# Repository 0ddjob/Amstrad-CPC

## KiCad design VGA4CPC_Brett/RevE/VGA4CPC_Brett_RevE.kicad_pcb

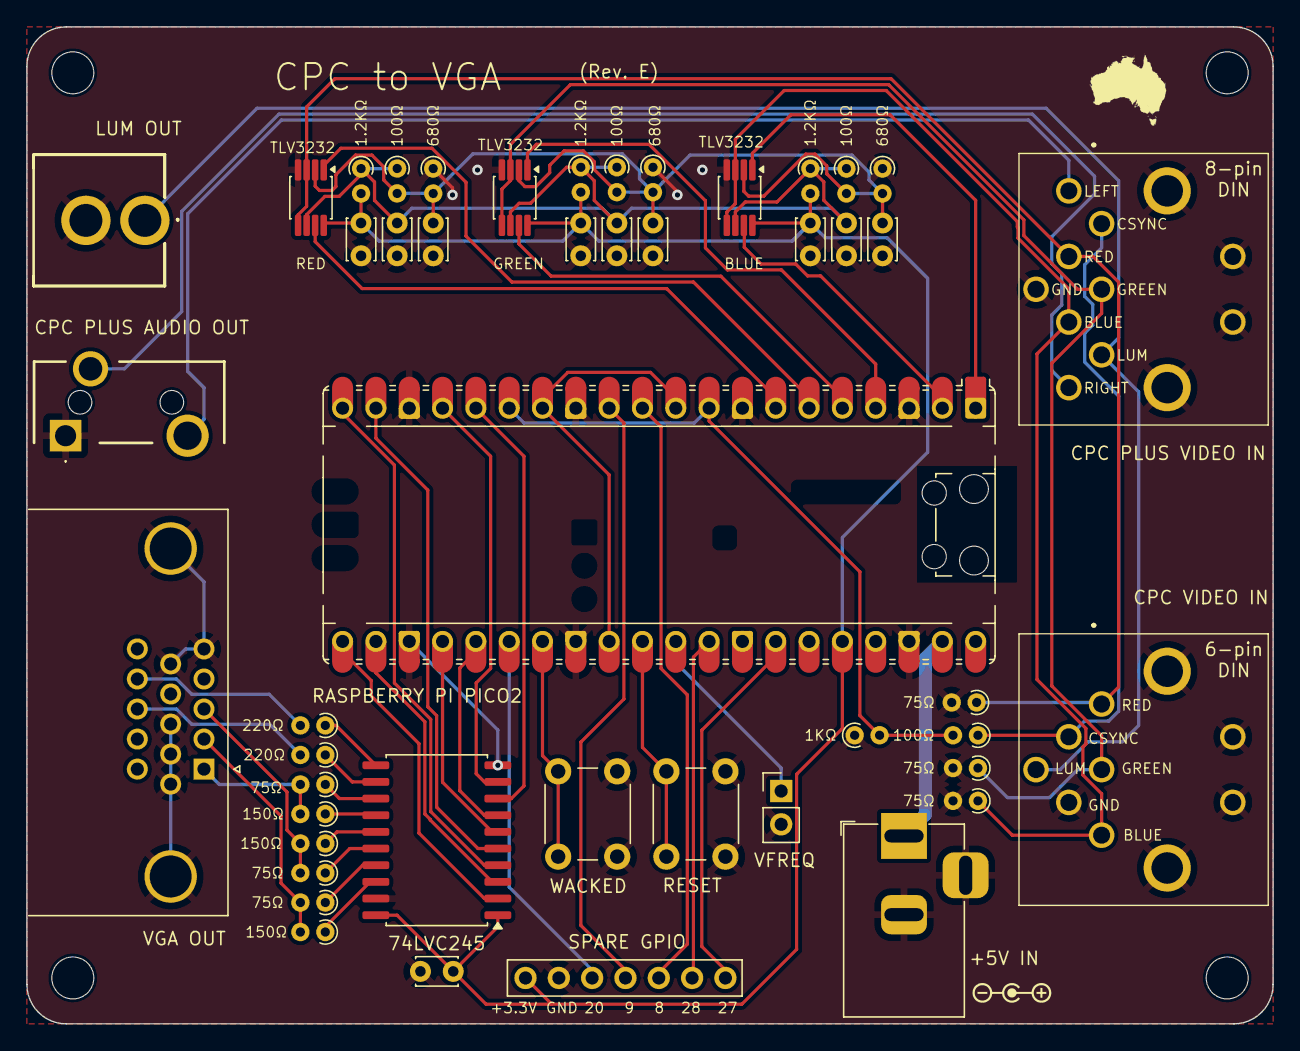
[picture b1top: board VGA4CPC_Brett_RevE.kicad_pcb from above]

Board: 2 copper layers, 95.0 x 76.0 mm, 51 parts (0 on the bottom side), 49 nets.

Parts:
C1, C2, C3, C4, C5, C6, C7, C8, C9, C10: 100nF; C_Disc_D3.0mm_W2.0mm_P2.50mm
H1, H2, H3, H4: MountingHole; MountingHole_3.2mm_M3
J1: CPC VIDEO IN; SDF80J
J2: LUM OUT; 1560099E
J3: +5V IN; BarrelJack_Horizontal
J4: VFREQ; PinHeader_1x02_P2.54mm_Vertical
J5: SPARE GPIO; PinHeader_1x07_P2.54mm_Vertical
J6: VGA OUT; DSUB-15-HD_Socket_Horizontal_P2.29x2.54mm_EdgePinOffset8.35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
J7: CPC PLUS VIDEO IN; SDF80J
J8: CPC PLUS AUDIO OUT; SJ335083ATR
R1, R2, R3, R7, R8, R11: 75Ω; R_Axial_DIN0204_L3.6mm_D1.6mm_P1.90mm_Vertical
R4, R16, R18, R21: 100Ω; R_Axial_DIN0204_L3.6mm_D1.6mm_P1.90mm_Vertical
R5: 1KΩ; R_Axial_DIN0204_L3.6mm_D1.6mm_P1.90mm_Vertical
R6, R9, R10: 150Ω; R_Axial_DIN0204_L3.6mm_D1.6mm_P1.90mm_Vertical
R12, R13: 220Ω; R_Axial_DIN0204_L3.6mm_D1.6mm_P1.90mm_Vertical
R14, R15, R20: 1.2KΩ; R_Axial_DIN0204_L3.6mm_D1.6mm_P1.90mm_Vertical
R17, R19, R22: 680Ω; R_Axial_DIN0204_L3.6mm_D1.6mm_P1.90mm_Vertical
SW1: RESET; SW_PUSH_6mm
SW2: WACKED; SW_PUSH_6mm
U1: RASPBERRY PI PICO2; RaspberryPi_Pico_Common_Unspecified
U2: 74LVC245; SOIC-20W_7.5x12.8mm_P1.27mm
U3, U4, U5: TLV3232; VSSOP-8_3x3mm_P0.65mm

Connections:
+3.3V: C1.2, C7.1, C9.1, C10.1, J5.7, R14.2, R15.2, R20.2, U1.36 (3V3), U2.1 (A->B), U2.20 (VCC), U3.8 (VCC), U4.8 (VCC), U5.8 (VCC)
+5V: J3.1, U1.39 (VSYS)
/B_{0}: U1.1 (GPIO0), U3.1 (1OUT)
/B_{1}: U1.2 (GPIO1), U3.7 (2OUT)
/CPC_AUDIO_L: J7.6, J8.T
/CPC_AUDIO_R: J7.7, J8.R
/CPC_B: J1.3, J7.5, R1.1, U3.3 (1IN+), U3.5 (2IN+)
/CPC_CSYNC: J1.4, J7.1, R4.1
/CPC_G: J1.2, J7.2, R2.1, U5.3 (1IN+), U5.5 (2IN+)
/CPC_LUM: J1.6, J2.1 (In), J7.3
/CPC_R: J1.1, J7.4, R3.1, U4.3 (1IN+), U4.5 (2IN+)
/CSYNC: R4.2, R5.2, U1.9 (GPIO6), U1.15 (GPIO11)
/GPIO8: J5.3, U1.11 (GPIO8)
/GPIO9: J5.4, U1.12 (GPIO9)
/GPIO20: J5.5, U1.26 (GPIO20)
/GPIO27: J5.2, U1.32 (GPIO27_ADC1)
/GPIO28: J5.1, U1.34 (GPIO28_ADC2)
/G_{0}: U1.4 (GPIO2), U5.1 (1OUT)
/G_{1}: U1.5 (GPIO3), U5.7 (2OUT)
/INT_VSYNC: U1.10 (GPIO7), U1.14 (GPIO10), U1.29 (GPIO22)
/LOWER: C2.1, C3.1, C4.1, R16.2, R17.2, R18.2, R19.2, R21.2, R22.2, U3.2 (1IN-), U4.2 (1IN-), U5.2 (1IN-)
/R_{0}: U1.6 (GPIO4), U4.1 (1OUT)
/R_{1}: U1.7 (GPIO5), U4.7 (2OUT)
/UPPER: C5.1, C6.1, C8.1, R14.1, R15.1, R16.1, R18.1, R20.1, R21.1, U3.6 (2IN-), U4.6 (2IN-), U5.6 (2IN-)
/VGA_B: J6.3, R8.2, R9.2
/VGA_B_{0}: U1.19 (GPIO14), U2.5 (A3)
/VGA_B_{1}: U1.20 (GPIO15), U2.4 (A2)
/VGA_G: J6.2, R6.2, R7.2
/VGA_G_{0}: U1.21 (GPIO16), U2.2 (A0)
/VGA_G_{1}: U1.22 (GPIO17), U2.3 (A1)
/VGA_HSYNC: U1.16 (GPIO12), U2.8 (A6)
/VGA_HSYNC_{B}: J6.13, R12.2
/VGA_R: J6.1, R10.2, R11.2
/VGA_R_{0}: U1.24 (GPIO18), U2.6 (A4)
/VGA_R_{1}: U1.25 (GPIO19), U2.7 (A5)
/VGA_VSYNC: U1.17 (GPIO13), U2.9 (A7)
/VGA_VSYNC_{B}: J6.14, R13.2
GND: C1.1, C2.2, C3.2, C4.2, C5.2, C6.2, C7.2, C8.2, C9.2, C10.2, J1.5, J2.2 (Ext), J3.2, J4.2, J5.6, J6.0, J6.5, J6.6, J6.7, J6.8, J6.10, J7.8, J8.S, R1.2, R2.2, R3.2, R5.1, R17.1, R19.1, R22.1, SW1.1, SW2.2, U1.3 (GND), U1.8 (GND), U1.13 (GND), U1.18 (GND), U1.23 (GND), U1.28 (GND), U1.38 (GND), U2.10 (GND), U2.19 (CE), U3.4 (GND), U4.4 (GND), U5.4 (GND)
unnamed: J4.1, U1.31 (GPIO26_ADC0)
unnamed: SW2.1, U1.27 (GPIO21)
unnamed: SW1.2, U1.30 (RUN)
unnamed: R6.1, U2.18 (B0)
unnamed: R7.1, U2.17 (B1)
unnamed: R8.1, U2.16 (B2)
unnamed: R9.1, U2.15 (B3)
unnamed: R10.1, U2.14 (B4)
unnamed: R11.1, U2.13 (B5)
unnamed: R12.1, U2.12 (B6)
unnamed: R13.1, U2.11 (B7)

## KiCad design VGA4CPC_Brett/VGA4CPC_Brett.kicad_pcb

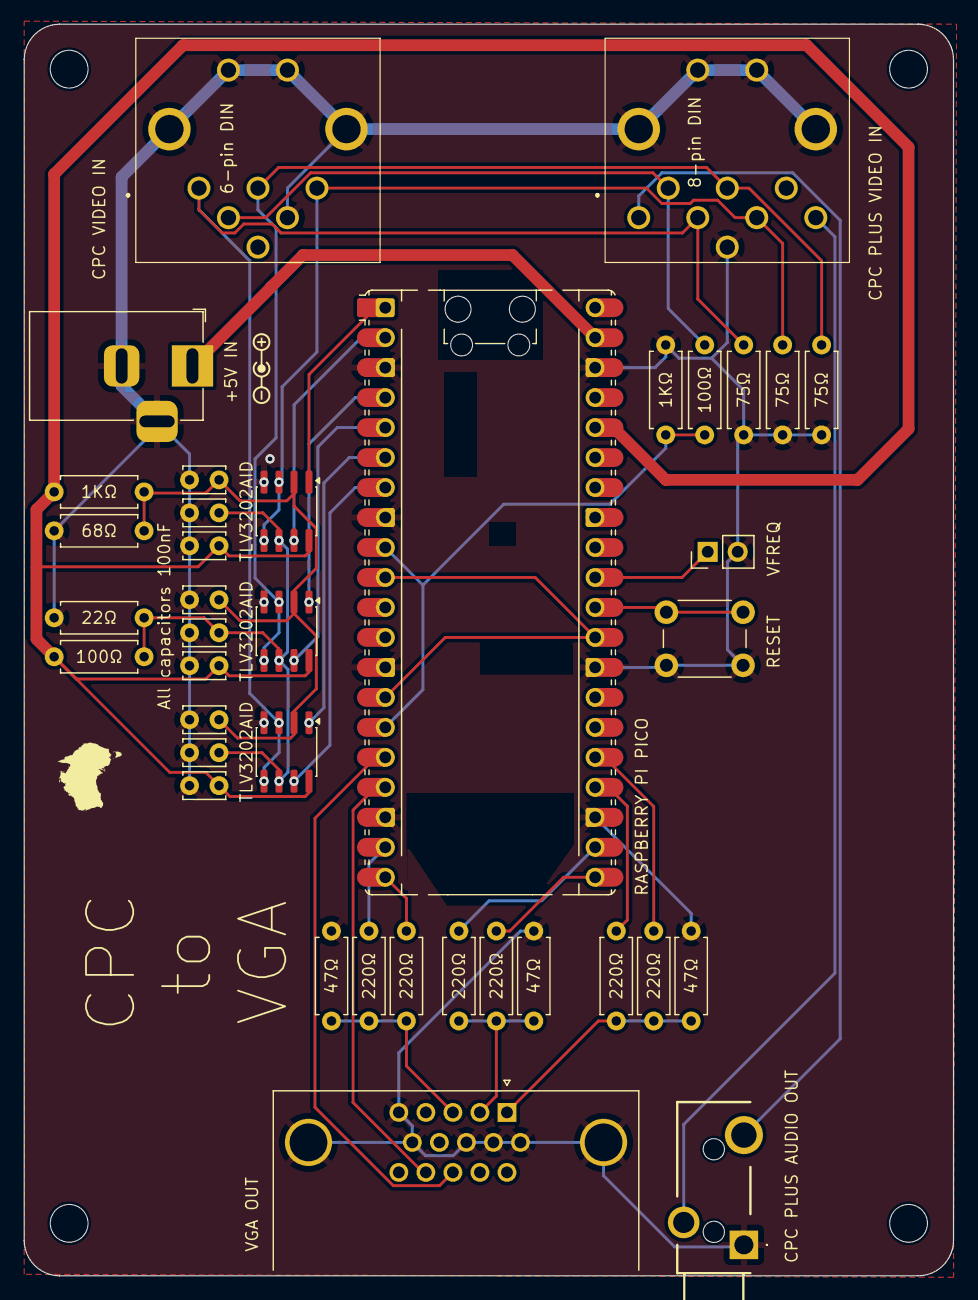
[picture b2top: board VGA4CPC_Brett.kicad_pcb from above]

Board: 2 copper layers, 78.7 x 106.0 mm, 42 parts (0 on the bottom side), 32 nets.

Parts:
C1, C2, C3, C4, C5, C6, C7, C8, C9: 100nF; C_Disc_D3.4mm_W2.1mm_P2.50mm
H1, H2, H3, H4: MountingHole; MountingHole_3.2mm_M3
J1: +5V IN; BarrelJack_Horizontal
J2: CPC PLUS AUDIO OUT; SJ335083ATR
J3: CPC PLUS VIDEO IN; SDF80J
J4: CPC VIDEO IN; SDF80J
J5: VFREQ; PinHeader_1x02_P2.54mm_Vertical
J6: VGA OUT; DSUB-15-HD_Socket_Horizontal_P2.29x2.54mm_EdgePinOffset8.35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
R1, R13: 1KΩ; R_Axial_DIN0207_L6.3mm_D2.5mm_P7.62mm_Horizontal
R2, R12: 100Ω; R_Axial_DIN0207_L6.3mm_D2.5mm_P7.62mm_Horizontal
R3: 68Ω; R_Axial_DIN0207_L6.3mm_D2.5mm_P7.62mm_Horizontal
R4: 22Ω; R_Axial_DIN0207_L6.3mm_D2.5mm_P7.62mm_Horizontal
R5, R14, R18: 75Ω; R_Axial_DIN0207_L6.3mm_D2.5mm_P7.62mm_Horizontal
R6, R8, R9, R11, R15, R17: 220Ω; R_Axial_DIN0207_L6.3mm_D2.5mm_P7.62mm_Horizontal
R7, R10, R16: 47Ω; R_Axial_DIN0207_L6.3mm_D2.5mm_P7.62mm_Horizontal
SW1: RESET; SW_PUSH_6mm
U1, U2, U4: TLV3202AID; SOIC-8_3.9x4.9mm_P1.27mm
U3: RASPBERRY PI PICO; RaspberryPi_Pico_Common_Unspecified

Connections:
+3.3V: C1.1, C4.1, C7.1, R1.1, R2.1, U1.8 (VCC), U2.8 (VCC), U3.36 (3V3), U4.8 (VCC)
+5V: J1.1, U3.39 (VSYS)
/200mV: C2.1, C5.1, C8.1, R1.2, R3.1, U1.2 (1IN-), U2.2 (1IN-), U4.2 (1IN-)
/600mV: C3.1, C6.1, C9.1, R2.2, R4.1, U1.6 (2IN-), U2.6 (2IN-), U4.6 (2IN-)
/B_{0}: U1.1 (1OUT), U3.1 (GPIO0)
/B_{1}: U1.7 (2OUT), U3.2 (GPIO1)
/CPC_AUDIO_L: J2.T, J3.6
/CPC_AUDIO_R: J2.R, J3.7
/CPC_B: J3.5, J4.3, R5.1, U1.3 (1IN+), U1.5 (2IN+)
/CPC_CSYNC: J3.1, J4.4, R12.1
/CPC_G: J3.2, J4.2, R14.1, U2.3 (1IN+), U2.5 (2IN+)
/CPC_R: J3.4, J4.1, R18.1, U4.3 (1IN+), U4.5 (2IN+)
/CSYNC: R12.2, R13.1, U3.9 (GPIO6), U3.15 (GPIO11)
/G_{0}: U2.1 (1OUT), U3.4 (GPIO2)
/G_{1}: U2.7 (2OUT), U3.5 (GPIO3)
/INT_VSYNC: U3.10 (GPIO7), U3.14 (GPIO10), U3.29 (GPIO22)
/R_{0}: U3.6 (GPIO4), U4.1 (1OUT)
/R_{1}: U3.7 (GPIO5), U4.7 (2OUT)
/VGA_B: J6.3, R15.2, R16.2, R17.2
/VGA_G: J6.2, R6.2, R7.1, R8.2
/VGA_HSYNC: J6.13, U3.16 (GPIO12)
/VGA_R: J6.1, R9.2, R10.1, R11.2
/VGA_VSYNC: J6.14, U3.17 (GPIO13)
GND: C1.2, C2.2, C3.2, C4.2, C5.2, C6.2, C7.2, C8.2, C9.2, J1.2, J2.S, J3.8, J4.5, J5.2, J6.0, J6.5, J6.6, J6.7, J6.8, J6.10, R3.2, R4.2, R5.2, R7.2, R10.2, R13.2, R14.2, R16.1, R18.2, SW1.1, U1.4 (GND), U2.4 (GND), U3.3 (GND), U3.8 (GND), U3.13 (GND), U3.18 (GND), U3.23 (GND), U3.28 (GND), U3.38 (GND), U4.4 (GND)
unnamed: J5.1, U3.31 (GPIO26_ADC0)
unnamed: R15.1, U3.19 (GPIO14)
unnamed: R17.1, U3.20 (GPIO15)
unnamed: R6.1, U3.21 (GPIO16)
unnamed: R8.1, U3.22 (GPIO17)
unnamed: R9.1, U3.24 (GPIO18)
unnamed: R11.1, U3.25 (GPIO19)
unnamed: SW1.2, U3.30 (RUN)

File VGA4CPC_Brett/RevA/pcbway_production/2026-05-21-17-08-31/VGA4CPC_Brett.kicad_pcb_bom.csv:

Designator,Quantity,Value,Footprint,Package,MPN,DNP,Mount_Type,Description,Height,Mouser Part Number,Mouser Price/Stock,Manufacturer_Name
"C1, C2, C3, C4, C5, C6, C7, C8, C9",9,100nF,C_Disc_D3.4mm_W2.1mm_P2.50mm,,,,tht,,,,,
"H1, H2, H3, H4",4,MountingHole,MountingHole_3.2mm_M3,,,,tht,,,,,
J1,1,+5V IN,BarrelJack_Horizontal,,,,tht,DC Barrel Jack,,,,
J2,1,CPC PLUS AUDIO OUT,SJ335083ATR,,,,tht,"Audio Jack, 3 Poles (Stereo / TRS)",,,,
J3,1,CPC PLUS VIDEO IN,SDF80J,,,,tht,Same Sky SDF-80J 8-pin DIN socket,,,,
J4,1,CPC VIDEO IN,SDF80J,,,,tht,Same Sky SDF-60J 6-pin DIN Socket,,,,
J5,1,VFREQ,PinHeader_1x02_P2.54mm_Vertical,,,,tht,"Generic connector, single row, 01x02, script generated (kicad-library-utils/schlib/autogen/connector/)",,,,
J6,1,VGA OUT,DSUB-15-HD_Socket_Horizontal_P2.29x2.54mm_EdgePinOffset8.35mm_Housed_MountingHolesOffset10.89mm,,,,tht,"15-pin D-SUB connector, socket (female), High density (3 columns), Triple Row, Generic, VGA-connector, Mounting Hole",,,,
"R1, R13",2,1KΩ,R_Axial_DIN0207_L6.3mm_D2.5mm_P7.62mm_Horizontal,,,,tht,"Resistor, small symbol",,,,
"R10, R16, R7",3,47Ω,R_Axial_DIN0207_L6.3mm_D2.5mm_P7.62mm_Horizontal,,,,tht,"Resistor, small symbol",,,,
"R11, R15, R17, R6, R8, R9",6,220Ω,R_Axial_DIN0207_L6.3mm_D2.5mm_P7.62mm_Horizontal,,,,tht,"Resistor, small symbol",,,,
"R12, R2",2,100Ω,R_Axial_DIN0207_L6.3mm_D2.5mm_P7.62mm_Horizontal,,,,tht,"Resistor, small symbol",,,,
"R14, R18, R5",3,75Ω,R_Axial_DIN0207_L6.3mm_D2.5mm_P7.62mm_Horizontal,,,,tht,"Resistor, small symbol",,,,
R3,1,68Ω,R_Axial_DIN0207_L6.3mm_D2.5mm_P7.62mm_Horizontal,,,,tht,"Resistor, small symbol",,,,
R4,1,22Ω,R_Axial_DIN0207_L6.3mm_D2.5mm_P7.62mm_Horizontal,,,,tht,"Resistor, small symbol",,,,
SW1,1,RESET,SW_PUSH_6mm,,,,tht,"Push button switch, generic, two pins",,,,
"U1, U2, U4",3,TLV3202AID,SOIC-8_3.9x4.9mm_P1.27mm,,TLV3202AID,,smt,"Dual, 40ns, microPower, Rail-to-Rail input  Comparator with Push-pull outputs",1.75,595-TLV3202AID,https://www.mouser.co.uk/ProductDetail/Texas-Instruments/TLV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,Texas Instruments
U3,1,RASPBERRY PI PICO,RaspberryPi_Pico_Common_Unspecified,,,,tht,"Versatile and inexpensive microcontroller module powered by RP2040 dual-core Arm Cortex-M0+ processor up to 133 MHz, 264kB SRAM, 2MB QSPI flash; also supports Raspberry Pi Pico 2",,,,
